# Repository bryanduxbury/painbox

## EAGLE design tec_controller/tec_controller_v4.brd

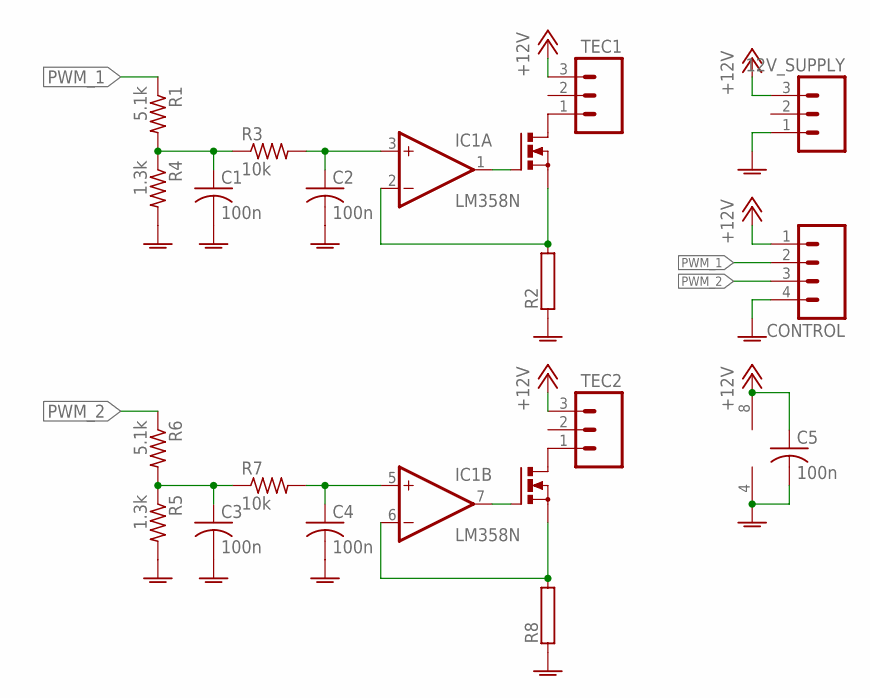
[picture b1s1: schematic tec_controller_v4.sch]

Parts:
12V_SUPPLY: M03POLAR; MOLEX-1X3
C1, C2, C3, C4, C5: 100n; C0805
CONTROL: M04POLAR; MOLEX-1X4
IC1: LM358N; DIL08
Q1, Q2: IRF512; TO220BV
R1, R6: 5.1k; M0805
R2, R8: RAC10; AC10
R3, R7: 10k; M0805
R4, R5: 1.3k; M0805
TEC1, TEC2: M03POLAR; MOLEX-1X3

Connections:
+12V: 12V_SUPPLY.3, C5.1, CONTROL.1, IC1.8 (V+), TEC1.3, TEC2.3
GNDA: 12V_SUPPLY.1, C1.2, C2.2, C3.2, C4.2, C5.2, CONTROL.4, IC1.4 (V-), R2.1, R4.2, R5.2, R8.1
unnamed: Q1.D, TEC1.1
unnamed: Q2.D, TEC2.1
unnamed: IC1.1 (OUT), Q1.G
unnamed: C1.1, R1.2, R3.1, R4.1
unnamed: C2.1, IC1.3 (+IN), R3.2
unnamed: IC1.2 (-IN), Q1.S, R2.2
unnamed: C3.1, R5.1, R6.2, R7.1
unnamed: C4.1, IC1.5 (+IN), R7.2
unnamed: IC1.7 (OUT), Q2.G
unnamed: IC1.6 (-IN), Q2.S, R8.2
PWM_1: CONTROL.2, R1.1
PWM_2: CONTROL.3, R6.1

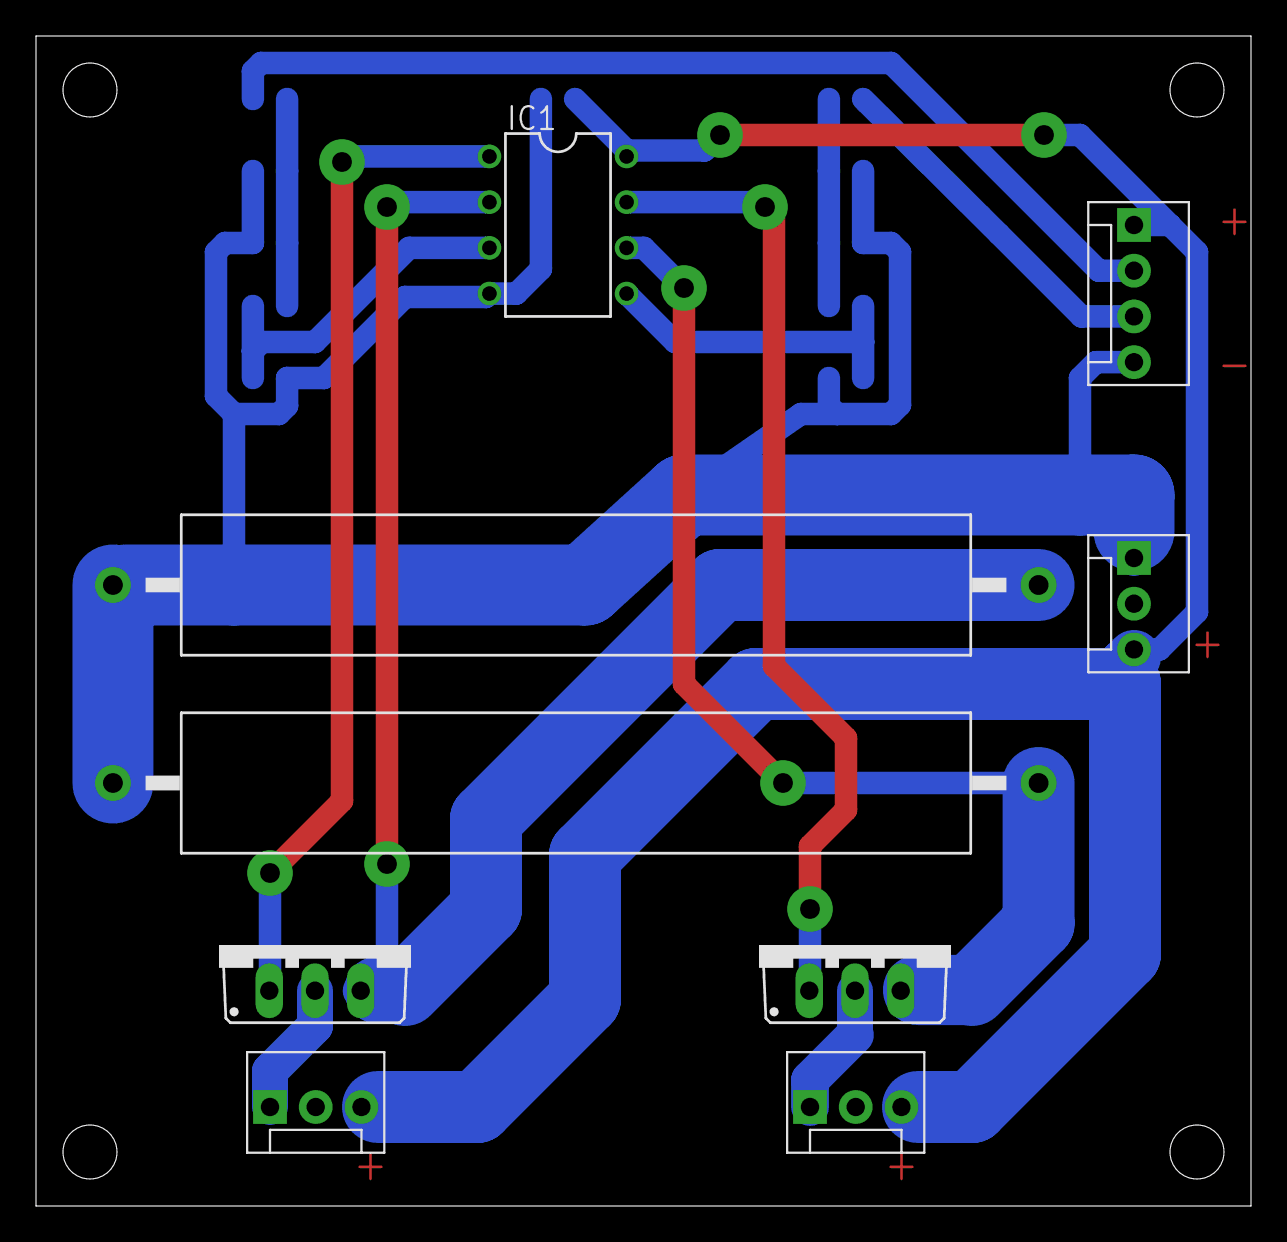
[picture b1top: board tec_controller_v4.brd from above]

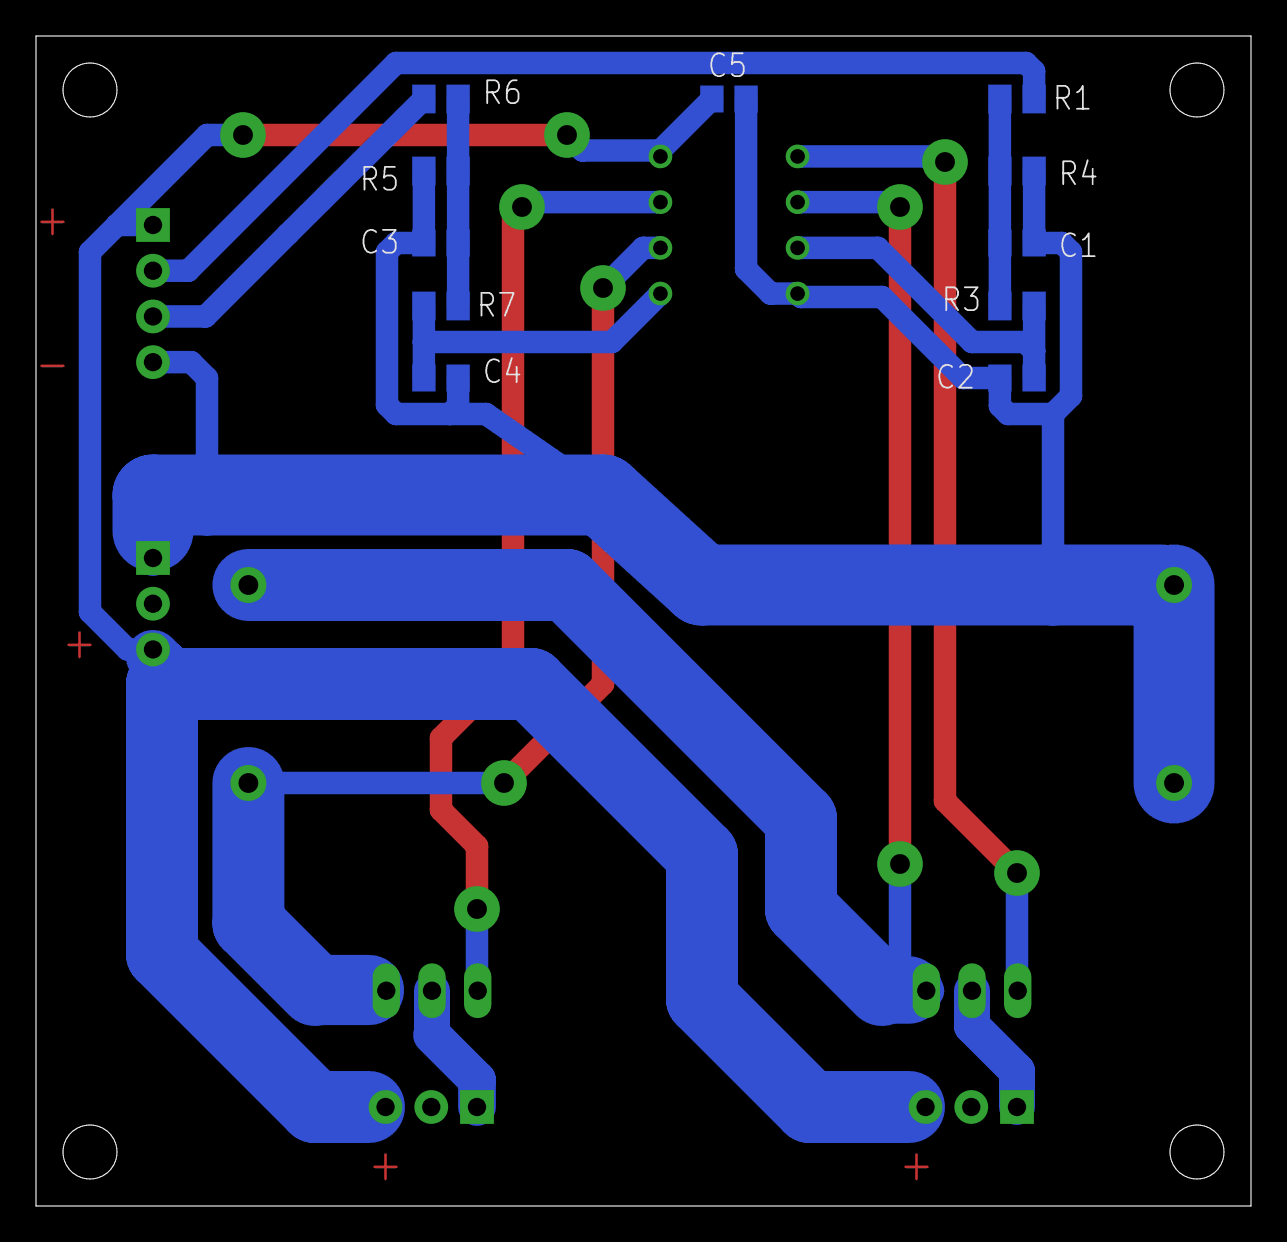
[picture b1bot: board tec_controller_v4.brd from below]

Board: 2 copper layers, 67.5 x 65.0 mm, 20 parts (11 on the bottom side), 14 nets.

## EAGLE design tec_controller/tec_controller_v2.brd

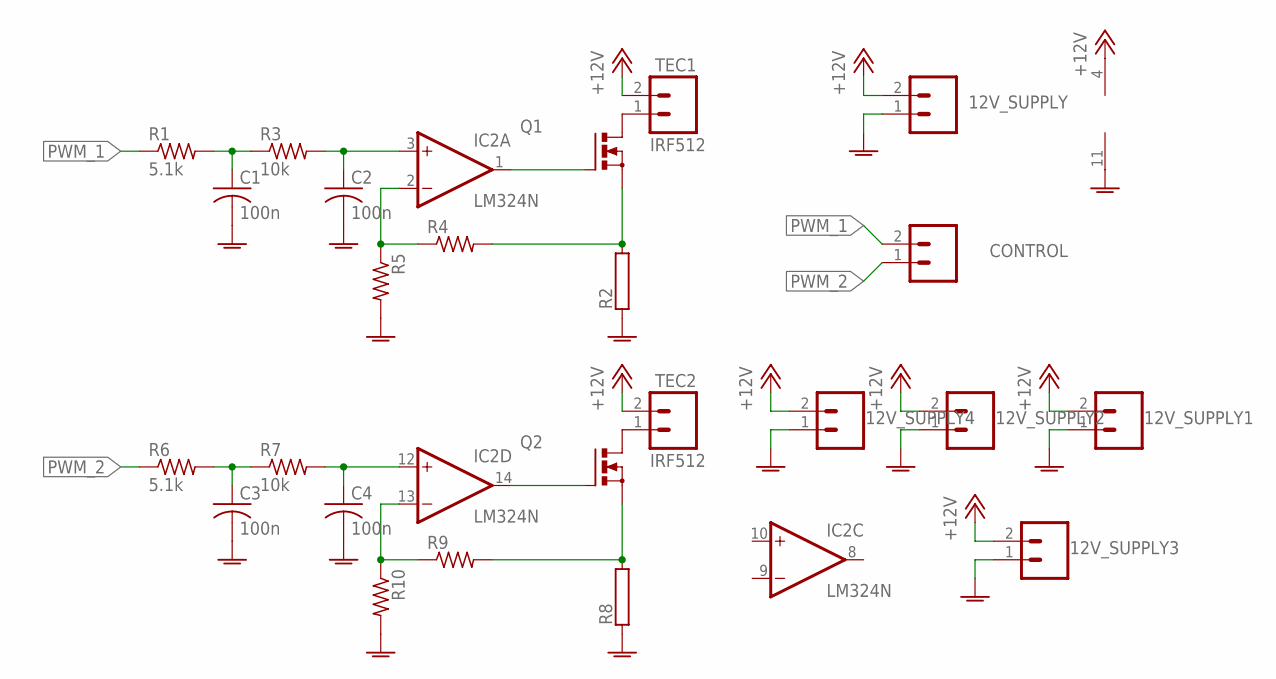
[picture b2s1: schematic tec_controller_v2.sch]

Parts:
12V_SUPPLY, 12V_SUPPLY1, 12V_SUPPLY2, 12V_SUPPLY3, 12V_SUPPLY4: M02LOCK_LONGPADS; 1X02_LOCK_LONGPADS
C1, C2, C3, C4: 100n; C0805
CONTROL: M02LOCK_LONGPADS; 1X02_LOCK_LONGPADS
IC2: LM324N; DIL14
Q1, Q2: IRF512; TO220BV
R1, R6: 5.1k; M0805
R2, R8: RAC10; AC10
R3, R7: 10k; M0805
R4, R5, R9, R10: R-US_M0805; M0805
TEC1, TEC2: M02LOCK_LONGPADS; 1X02_LOCK_LONGPADS

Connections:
+12V: 12V_SUPPLY.2, 12V_SUPPLY1.2, 12V_SUPPLY2.2, 12V_SUPPLY3.2, 12V_SUPPLY4.2, IC2.4 (V+), TEC1.2, TEC2.2
GNDA: 12V_SUPPLY.1, 12V_SUPPLY1.1, 12V_SUPPLY2.1, 12V_SUPPLY3.1, 12V_SUPPLY4.1, C1.2, C2.2, C3.2, C4.2, IC2.11 (V-), R2.1, R5.2, R8.1, R10.2
unnamed: Q1.D, TEC1.1
unnamed: Q1.S, R2.2, R4.2
unnamed: IC2.1 (OUT), Q1.G
unnamed: C1.1, R1.2, R3.1
unnamed: C2.1, IC2.3 (+IN), R3.2
unnamed: IC2.2 (-IN), R4.1, R5.1
unnamed: C3.1, R6.2, R7.1
unnamed: C4.1, IC2.12 (+IN), R7.2
unnamed: Q2.D, TEC2.1
unnamed: Q2.S, R8.2, R9.2
unnamed: IC2.14 (OUT), Q2.G
unnamed: IC2.13 (-IN), R9.1, R10.1
PWM_1: CONTROL.2, R1.1
PWM_2: CONTROL.1, R6.1

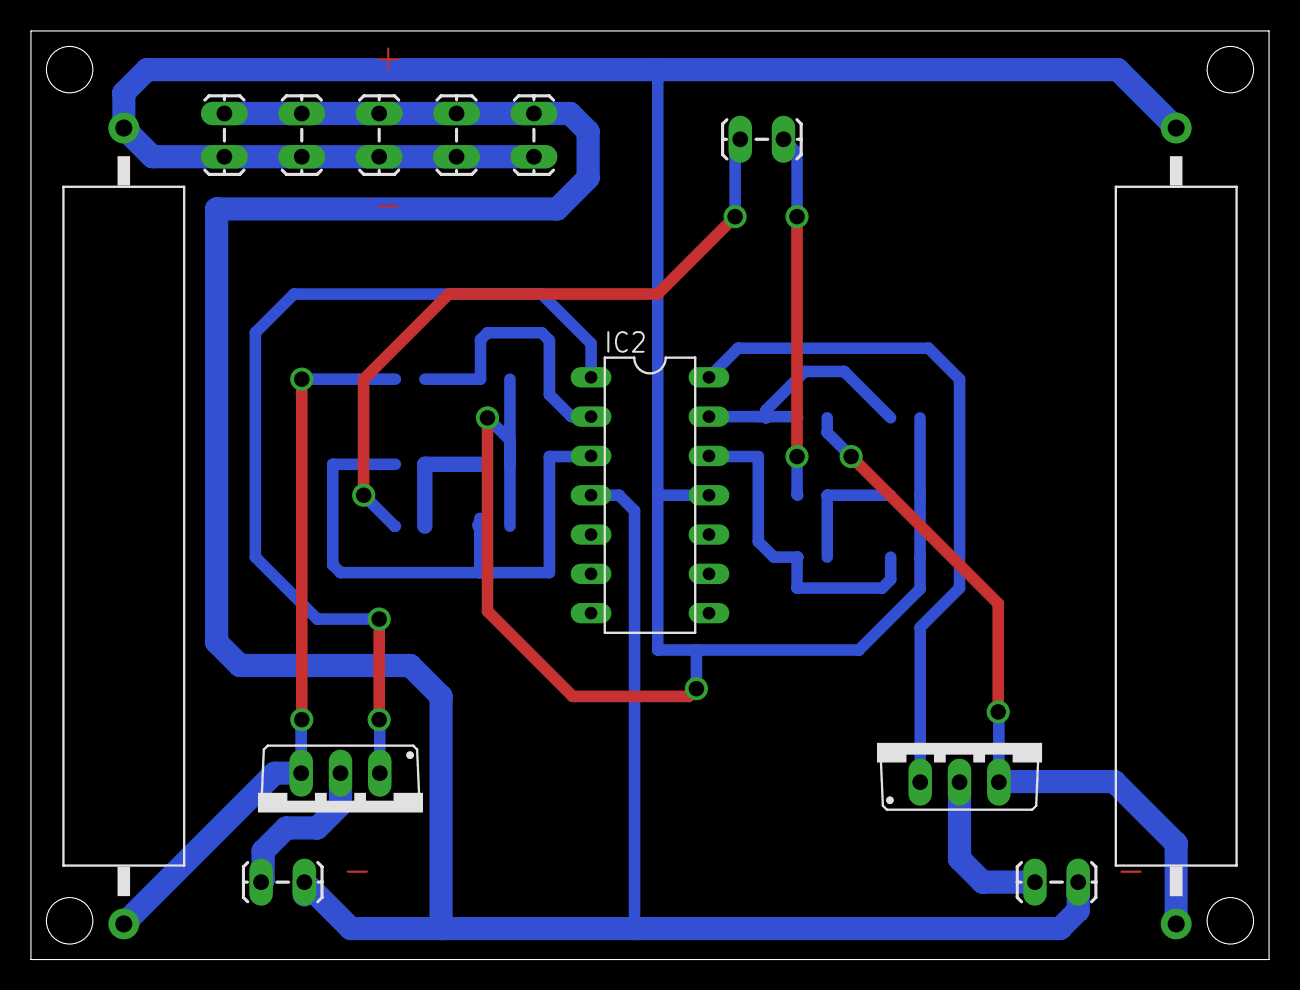
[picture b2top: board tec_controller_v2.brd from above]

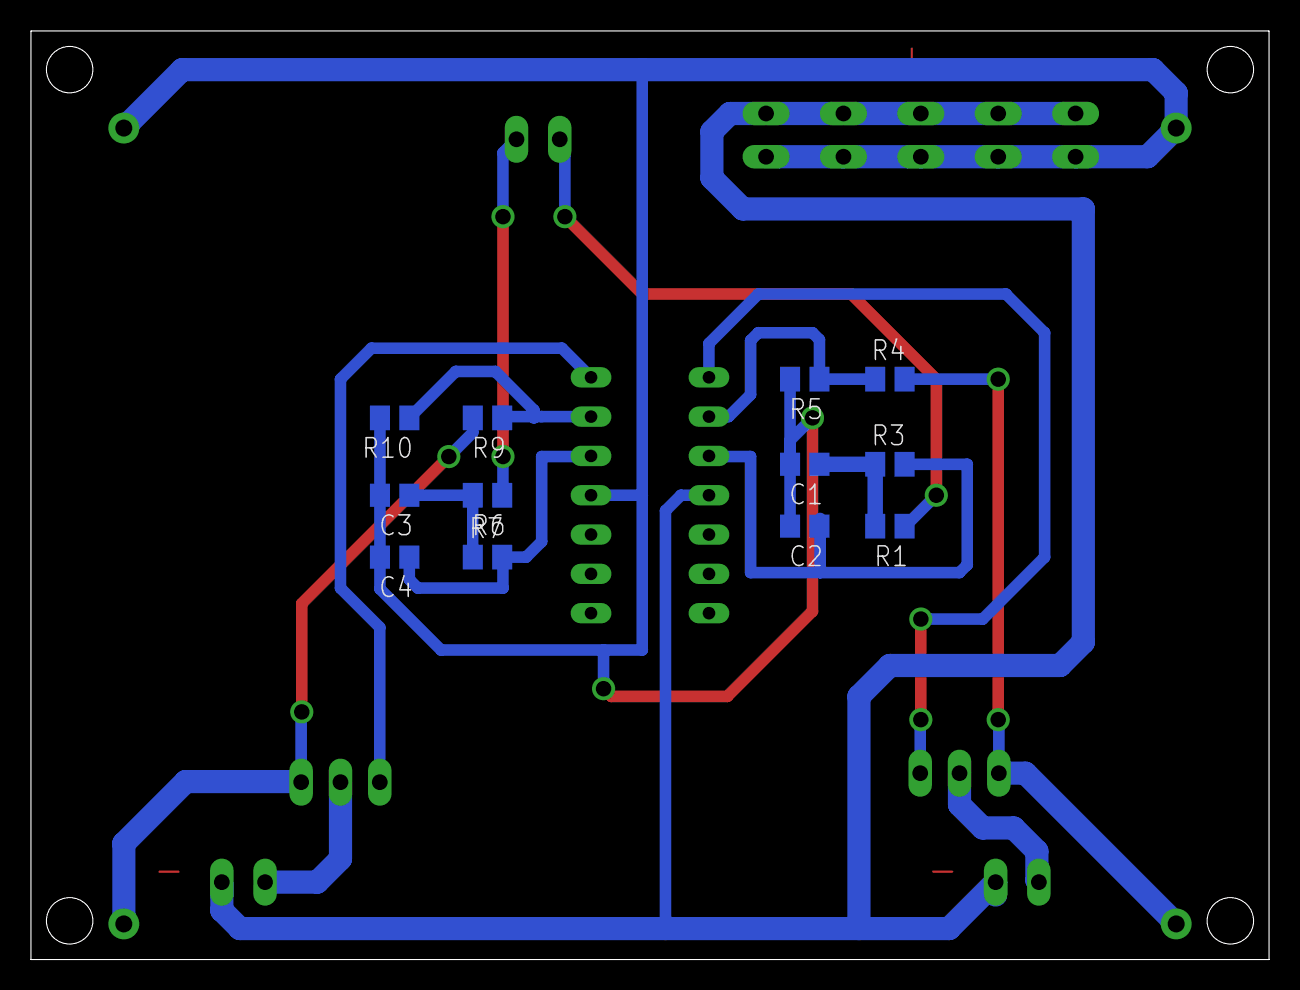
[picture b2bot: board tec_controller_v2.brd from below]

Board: 2 copper layers, 80.0 x 60.0 mm, 25 parts (12 on the bottom side), 16 nets.

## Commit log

2015-01-15 init commit
2015-01-15 add gitignore
2015-01-23 radiator changes
2015-02-02 first go at a thermistor reading helper class
2015-02-24 numerous experiments with scad
2015-02-24 code to read thermistors
2015-02-24 schematic and board for a pwm-to-constant-current-sink that can drive TECs
2015-02-24 gitignore for eagle temp files
2015-03-02 v2 of TEC controller board
2015-03-31 changes to final version of tec controller
2015-03-31 tec controller changes
2015-03-31 bending jig first draft
2015-03-31 bare skeleton of firmware
2015-04-24 yay working radiator block
2015-04-24 firmware WIP
2015-04-24 adjustments to tec controller board and schematic
2015-08-01 all-aluminum touch surface design
2015-08-01 waterblock carriage
2015-08-01 v4 tec controller
2015-08-16 hide away some deprecated designs

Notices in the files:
parts and their libraries:
SparkFun-Connectors: Licensing: Creative Commons ShareAlike 4.0 International - https://creativecommons.org/licenses/by-sa/4.0
